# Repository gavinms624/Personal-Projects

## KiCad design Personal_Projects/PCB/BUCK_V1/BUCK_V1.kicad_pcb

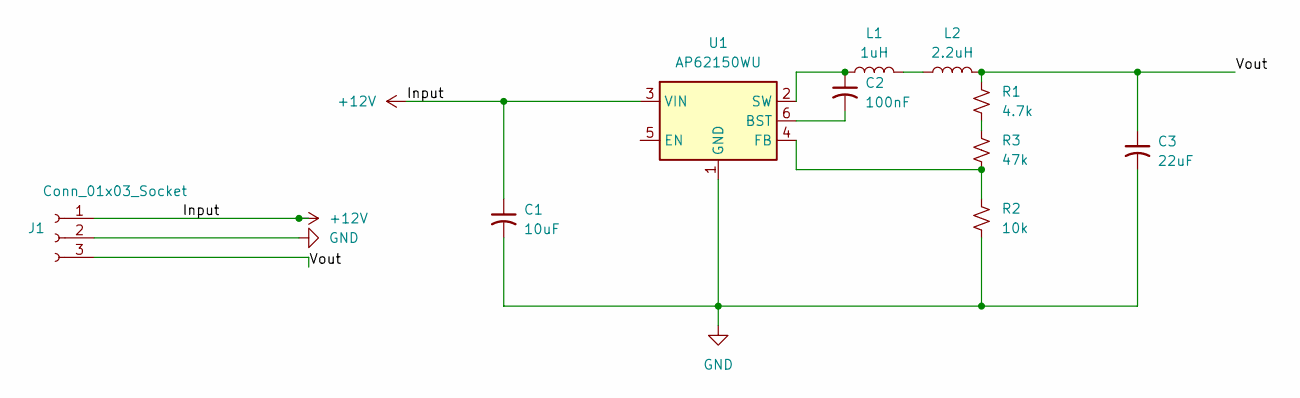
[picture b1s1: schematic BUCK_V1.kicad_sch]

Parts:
C1: 10uF; C_Disc_D5.0mm_W2.5mm_P5.00mm
C2: 100nF; C_Disc_D5.0mm_W2.5mm_P5.00mm
C3: 22uF; CP_Radial_D4.0mm_P2.00mm
J1: Conn_01x03_Socket; PinSocket_1x03_P2.54mm_Vertical
L1: 1uH; L_Radial_D7.0mm_P3.00mm
L2: 2.2uH; L_Radial_D7.0mm_P3.00mm
R1: 4.7k; R_Axial_DIN0309_L9.0mm_D3.2mm_P12.70mm_Horizontal
R2: 10k; R_Axial_DIN0309_L9.0mm_D3.2mm_P12.70mm_Horizontal
R3: 47k; R_Axial_DIN0309_L9.0mm_D3.2mm_P12.70mm_Horizontal
U1: AP62150WU; TSOT-23-6

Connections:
+12V: C1.1, J1.1, U1.3 (VIN)
/Vout: C3.1, J1.3, L2.2, R1.1
GND: C1.2, C3.2, J1.2, R2.2, U1.1 (GND)
unnamed: L1.2, L2.1
unnamed: R1.2, R3.1
unnamed: C2.2, U1.6 (BST)
unnamed: R2.1, R3.2, U1.4 (FB)
unnamed: C2.1, L1.1, U1.2 (SW)

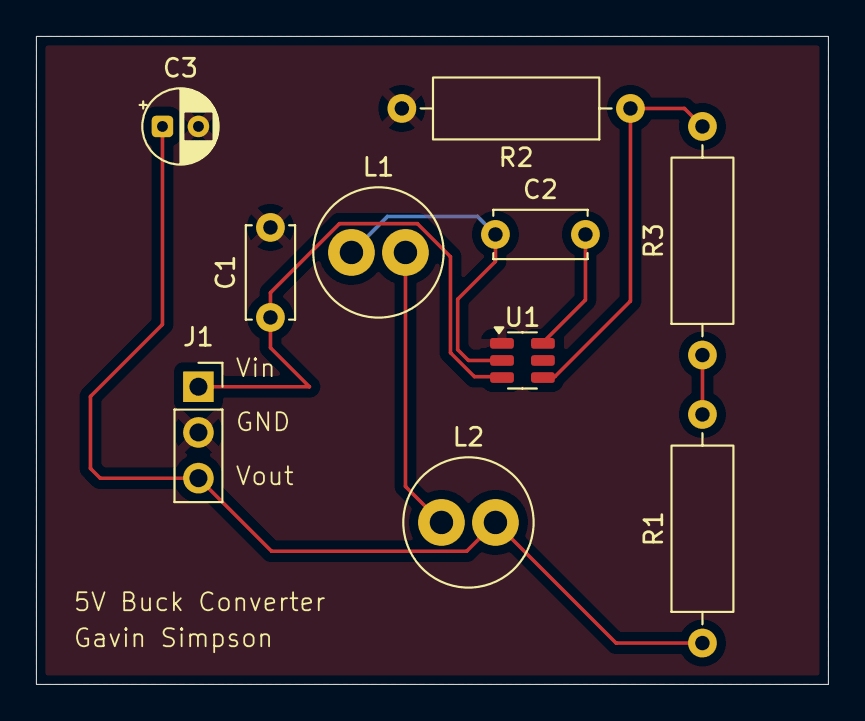
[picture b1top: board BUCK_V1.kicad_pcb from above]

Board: 2 copper layers, 44.0 x 36.0 mm, 10 parts (0 on the bottom side), 8 nets.

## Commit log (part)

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2026-03-02 first
2026-03-02 second
2026-03-02 eureka
2026-03-03 hopefully gitignore?
2026-03-05 pretty good sin
2026-03-05 pretty good sin v2
2026-03-05 gotta fix amp first
2026-03-07 update structure
2026-03-07 stashing
2026-03-07 fixed ltspice crap
2026-03-07 update BYU
2026-03-07 career folder
2026-03-08 stuff
2026-03-10 buffer stage
2026-03-11 sync
2026-03-18 lab7
